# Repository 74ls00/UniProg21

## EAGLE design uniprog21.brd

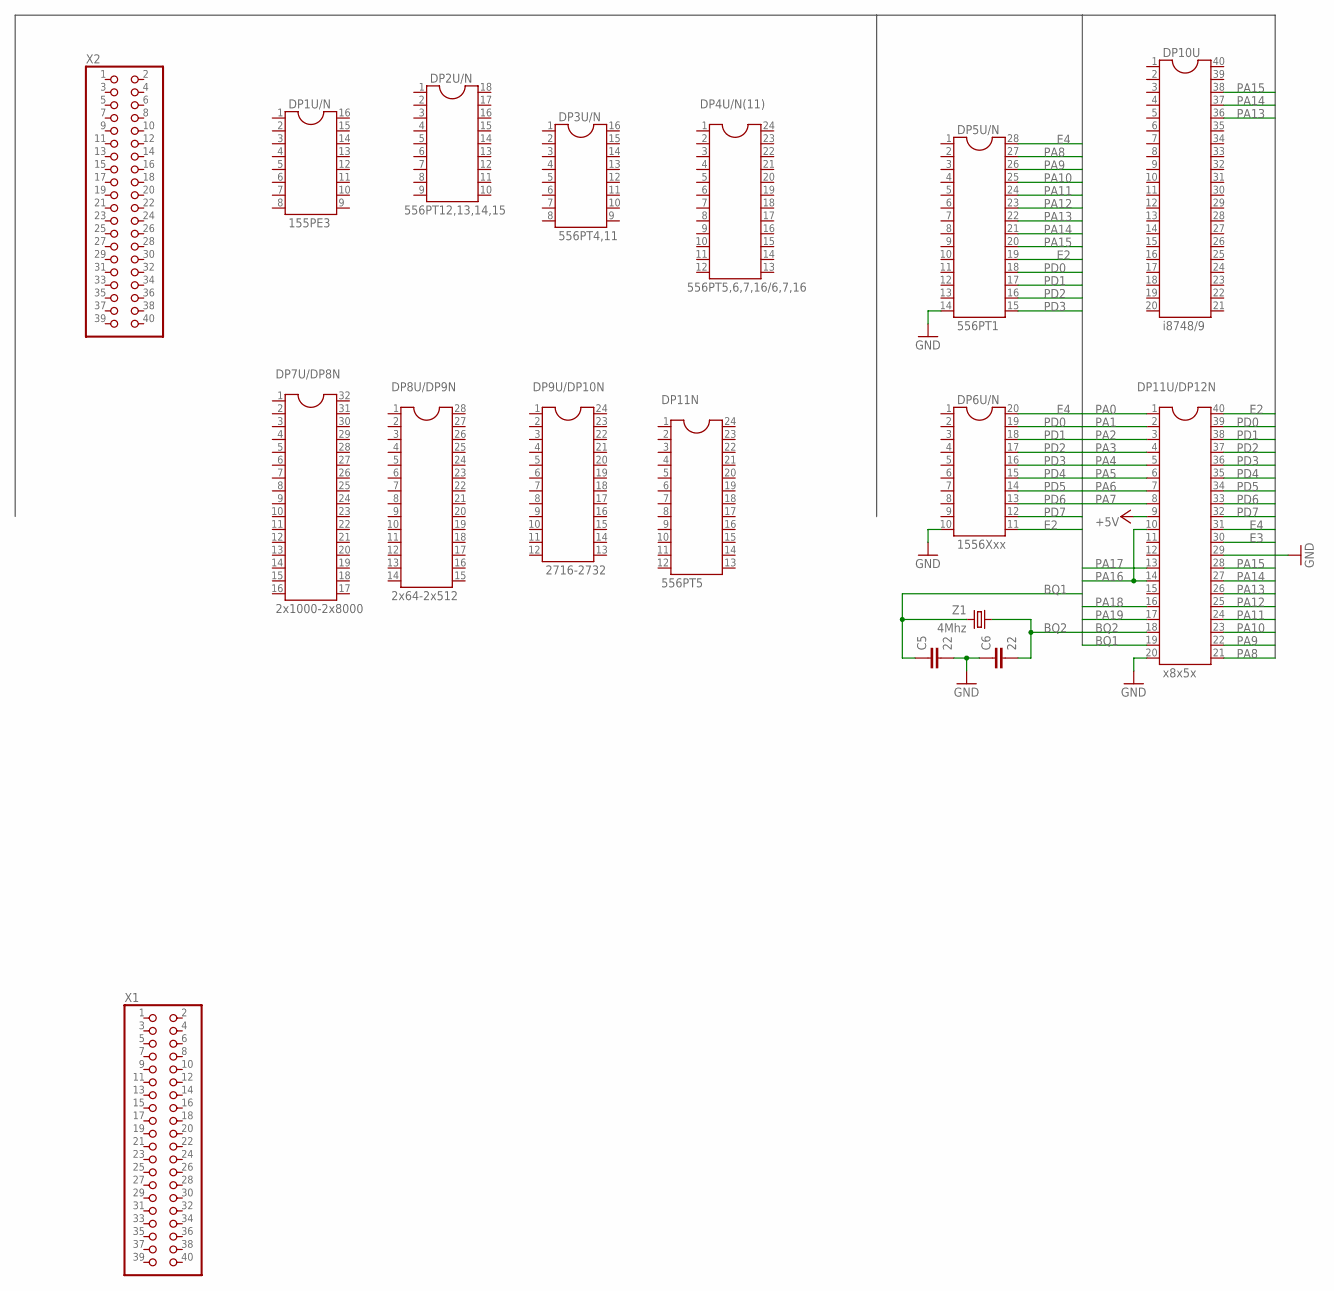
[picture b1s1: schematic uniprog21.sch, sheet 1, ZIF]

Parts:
C5, C6: 22; C0805
DP1U/N: 155РЕ3; SOCKET-16
DP2U/N: 556РТ12,13,14,15; SOCKET-18
DP3U/N: 556РТ4,11; SOCKET-16
DP4U/N(11): 556РТ5,6,7,16/6,7,16; DIL24-6
DP5U/N: 556РТ1; DIL28-6
DP6U/N: 1556Хxx; SOCKET-20
DP7U/DP8N: 2x1000-2x8000; DIL32
DP8U/DP9N: 2x64-2x512; DIL28-6
DP9U/DP10N: 2716-2732; DIL24-6
DP10U: i8748/9; DIL40
DP11N: 556РТ5; DIL24-6
DP11U/DP12N: x8x5x; DIL40
X1, X2: PINHD-2X20; 2X20
Z1: 4Mhz; HC49U-LM

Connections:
+5V: DP11U/DP12N.9; also elsewhere on the board
BQ1: C5.1, DP11U/DP12N.19, Z1.2
BQ2: C6.2, DP11U/DP12N.18, Z1.1
E2: DP5U/N.19, DP6U/N.11, DP11U/DP12N.40; also elsewhere on the board
E3: DP11U/DP12N.30; also elsewhere on the board
E4: DP5U/N.28, DP6U/N.20, DP11U/DP12N.31; also elsewhere on the board
GND: C5.2, C6.1, DP5U/N.14, DP6U/N.10, DP11U/DP12N.20, DP11U/DP12N.29; also elsewhere on the board
PA0: DP11U/DP12N.1; also elsewhere on the board
PA1: DP11U/DP12N.2; also elsewhere on the board
PA2: DP11U/DP12N.3
PA3: DP11U/DP12N.4
PA4: DP11U/DP12N.5
PA5: DP11U/DP12N.6
PA6: DP11U/DP12N.7
PA7: DP11U/DP12N.8
PA8: DP5U/N.27, DP11U/DP12N.21
PA9: DP5U/N.26, DP11U/DP12N.22
PA10: DP5U/N.25, DP11U/DP12N.23
PA11: DP5U/N.24, DP11U/DP12N.24
PA12: DP5U/N.23, DP11U/DP12N.25
PA13: DP5U/N.22, DP10U.36, DP11U/DP12N.26
PA14: DP5U/N.21, DP10U.37, DP11U/DP12N.27
PA15: DP5U/N.20, DP10U.38, DP11U/DP12N.28
PA16: DP11U/DP12N.10, DP11U/DP12N.14
PA17: DP11U/DP12N.13
PA18: DP11U/DP12N.16
PA19: DP11U/DP12N.17
PD0: DP5U/N.18, DP6U/N.19, DP11U/DP12N.39
PD1: DP5U/N.17, DP6U/N.18, DP11U/DP12N.38
PD2: DP5U/N.16, DP6U/N.17, DP11U/DP12N.37
PD3: DP5U/N.15, DP6U/N.16, DP11U/DP12N.36
PD4: DP6U/N.15, DP11U/DP12N.35
PD5: DP6U/N.14, DP11U/DP12N.34
PD6: DP6U/N.13, DP11U/DP12N.33
PD7: DP6U/N.12, DP11U/DP12N.32

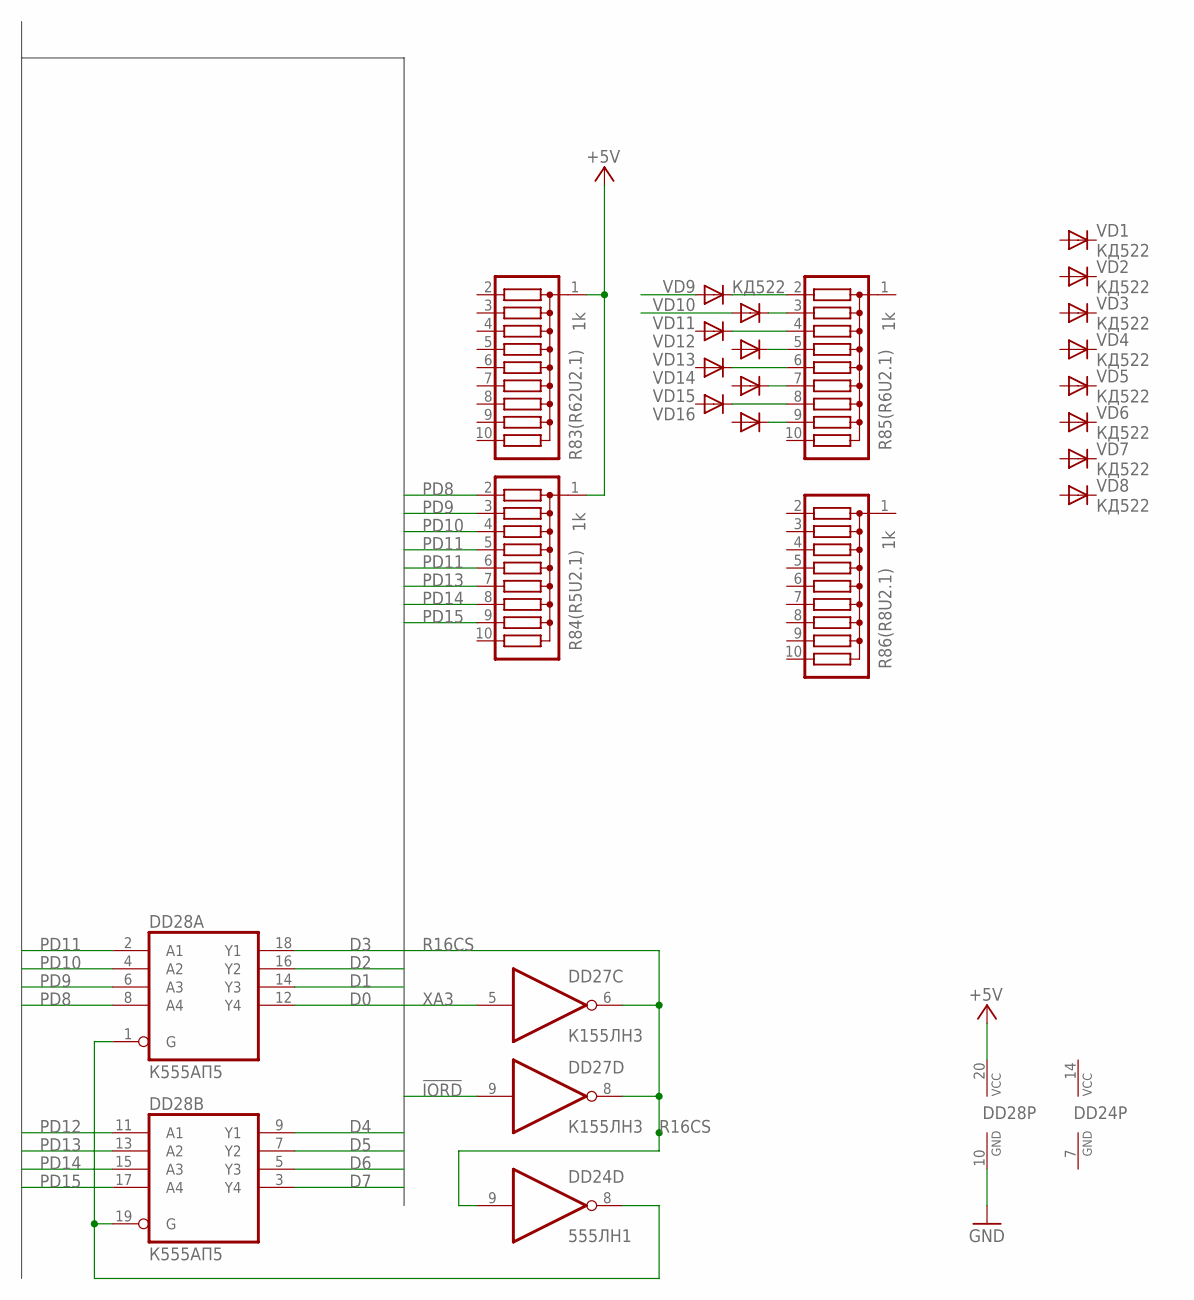
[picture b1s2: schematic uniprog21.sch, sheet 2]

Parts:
DD24: 555ЛН1; DIL14
DD27: К155ЛН3; DIL14
DD28: К555АП5; DIL20
R83(R62U2.1), R84(R5U2.1), R85(R6U2.1), R86(R8U2.1): 1k; SIL10
VD1, VD2, VD3, VD4, VD5, VD6, VD7, VD8, VD9, VD10, VD11, VD12, VD13, VD14, VD15, VD16: КД522; DO35-7

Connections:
!IORD: DD27.9 (I); also elsewhere on the board
+5V: DD28.20 (VCC), R83(R62U2.1).1, R84(R5U2.1).1; also elsewhere on the board
D0: DD28.12 (Y4); also elsewhere on the board
D1: DD28.14 (Y3); also elsewhere on the board
D2: DD28.16 (Y2); also elsewhere on the board
D3: DD28.18 (Y1); also elsewhere on the board
D4: DD28.9 (Y1); also elsewhere on the board
D5: DD28.7 (Y2); also elsewhere on the board
D6: DD28.5 (Y3); also elsewhere on the board
D7: DD28.3 (Y4); also elsewhere on the board
GND: DD24.7 (GND), DD28.10 (GND); also elsewhere on the board
unnamed: R85(R6U2.1).2, VD9.C
unnamed: DD24.8 (O), DD28.1 (G), DD28.19 (G)
unnamed: R85(R6U2.1).3, VD10.C
unnamed: R85(R6U2.1).4, VD11.C
unnamed: R85(R6U2.1).5, VD12.C
unnamed: R85(R6U2.1).6, VD13.C
unnamed: R85(R6U2.1).7, VD14.C
unnamed: R85(R6U2.1).8, VD15.C
unnamed: R85(R6U2.1).9, VD16.C
PD8: DD28.8 (A4), R84(R5U2.1).2
PD9: DD28.6 (A3), R84(R5U2.1).3
PD10: DD28.4 (A2), R84(R5U2.1).4
PD11: DD28.2 (A1), R84(R5U2.1).5, R84(R5U2.1).6
PD12: DD28.11 (A1)
PD13: DD28.13 (A2), R84(R5U2.1).7
PD14: DD28.15 (A3), R84(R5U2.1).8
PD15: DD28.17 (A4), R84(R5U2.1).9
R16CS: DD24.9 (I), DD27.6 (O), DD27.8 (O)
VCC: DD24.14 (VCC); also elsewhere on the board
XA3: DD27.5 (I); also elsewhere on the board

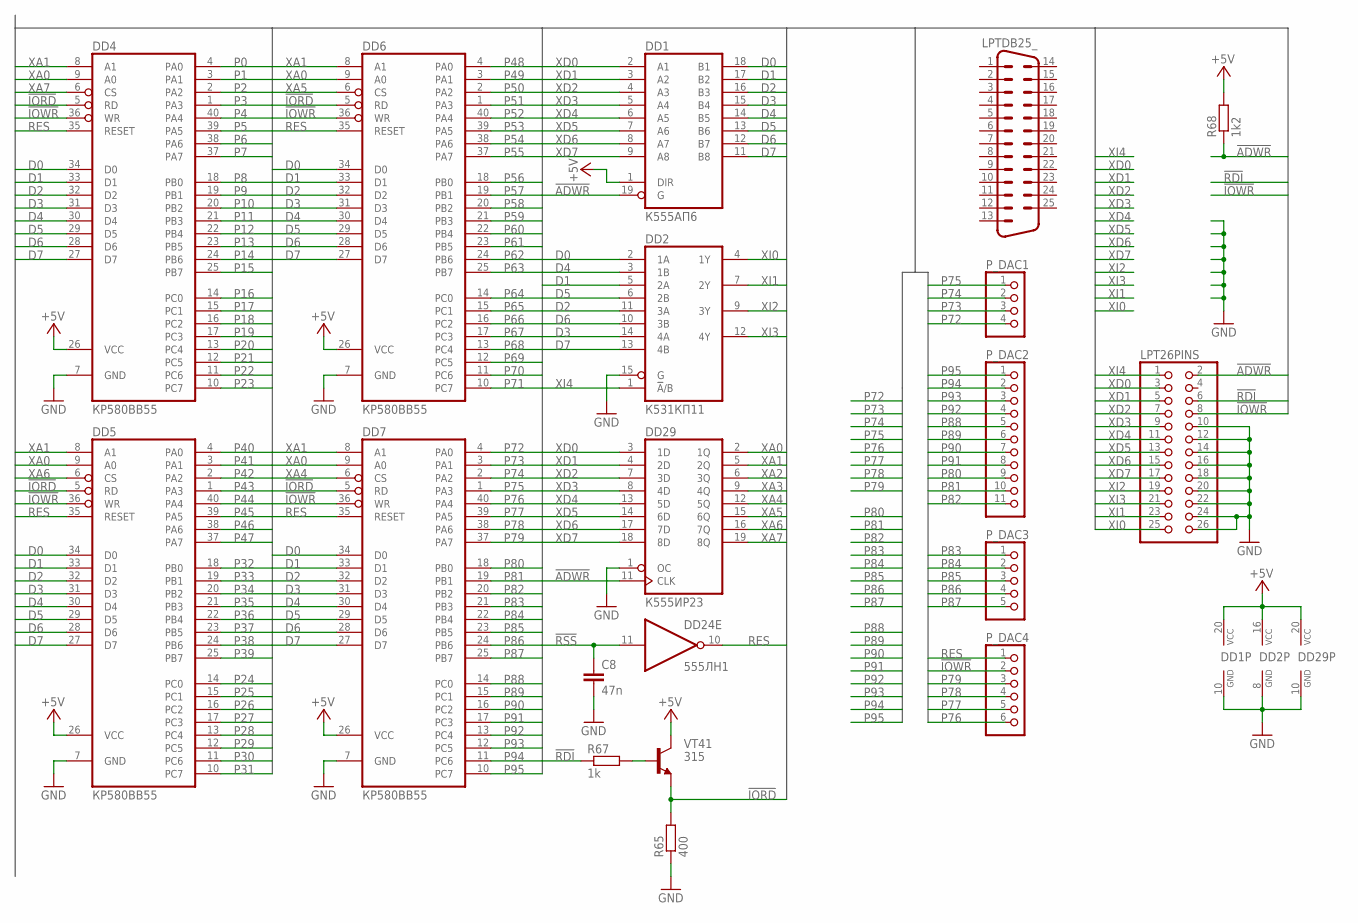
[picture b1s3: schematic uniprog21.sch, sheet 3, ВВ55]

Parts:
C8: 47n; C0805
DD1: К555АП6; DIL20
DD2: К531КП11; DIL16
DD4, DD5, DD6, DD7: КР580ВВ55; DIL40
DD24: 555ЛН1; DIL14
DD29: К555ИР23; DIL20
LPT26PINS: PINHD-2X13; 2X13
LPTDB25_: M25HP
P_DAC1: PINHD-1X4; 1X04
P_DAC2: PINHD-1X11; 1X11
P_DAC3: PINHD-1X5; 1X05
P_DAC4: PINHD-1X6; 1X06
R65: 400; R0805
R67: 1k; R0805
R68: 1k2; R0805
VT41: 315; SOT23

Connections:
!ADWR: DD1.19 (G), DD29.11 (CLK), LPT26PINS.2, R68.1
!IORD: DD4.5 (RD), DD5.5 (RD), DD6.5 (RD), DD7.5 (RD), R65.2, VT41.2 (E); also elsewhere on the board
!IOWR: DD4.36 (WR), DD5.36 (WR), DD6.36 (WR), DD7.36 (WR), LPT26PINS.8, P_DAC4.2
!RDI: LPT26PINS.6, R67.1
!RSS: C8.1, DD24.11 (I)
+5V: DD1.1 (DIR), DD1.20 (VCC), DD2.16 (VCC), DD4.26 (VCC), DD5.26 (VCC), DD6.26 (VCC), DD7.26 (VCC), DD29.20 (VCC), R68.2, VT41.3 (C); also elsewhere on the board
D0: DD1.18 (B1), DD2.2 (1A), DD4.34 (D0), DD5.34 (D0), DD6.34 (D0), DD7.34 (D0); also elsewhere on the board
D1: DD1.17 (B2), DD2.5 (2A), DD4.33 (D1), DD5.33 (D1), DD6.33 (D1), DD7.33 (D1); also elsewhere on the board
D2: DD1.16 (B3), DD2.11 (3A), DD4.32 (D2), DD5.32 (D2), DD6.32 (D2), DD7.32 (D2); also elsewhere on the board
D3: DD1.15 (B4), DD2.14 (4A), DD4.31 (D3), DD5.31 (D3), DD6.31 (D3), DD7.31 (D3); also elsewhere on the board
D4: DD1.14 (B5), DD2.3 (1B), DD4.30 (D4), DD5.30 (D4), DD6.30 (D4), DD7.30 (D4); also elsewhere on the board
D5: DD1.13 (B6), DD2.6 (2B), DD4.29 (D5), DD5.29 (D5), DD6.29 (D5), DD7.29 (D5); also elsewhere on the board
D6: DD1.12 (B7), DD2.10 (3B), DD4.28 (D6), DD5.28 (D6), DD6.28 (D6), DD7.28 (D6); also elsewhere on the board
D7: DD1.11 (B8), DD2.13 (4B), DD4.27 (D7), DD5.27 (D7), DD6.27 (D7), DD7.27 (D7); also elsewhere on the board
GND: C8.2, DD1.10 (GND), DD2.8 (GND), DD2.15 (G), DD4.7 (GND), DD5.7 (GND), DD6.7 (GND), DD7.7 (GND), DD24.7 (GND), DD29.1 (OC), DD29.10 (GND), LPT26PINS.10, LPT26PINS.12, LPT26PINS.14, LPT26PINS.16, LPT26PINS.18, LPT26PINS.20, LPT26PINS.22, LPT26PINS.24, LPT26PINS.26, R65.1; also elsewhere on the board
unnamed: R67.2, VT41.1 (B)
P0: DD4.4 (PA0); also elsewhere on the board
P1: DD4.3 (PA1); also elsewhere on the board
P2: DD4.2 (PA2)
P3: DD4.1 (PA3)
P4: DD4.40 (PA4)
P5: DD4.39 (PA5)
P6: DD4.38 (PA6)
P7: DD4.37 (PA7)
P8: DD4.18 (PB0); also elsewhere on the board
P9: DD4.19 (PB1); also elsewhere on the board
P10: DD4.20 (PB2)
P11: DD4.21 (PB3)
P12: DD4.22 (PB4)
P13: DD4.23 (PB5)
P14: DD4.24 (PB6)
P15: DD4.25 (PB7)
P16: DD4.14 (PC0)
P17: DD4.15 (PC1)
P18: DD4.16 (PC2)
P19: DD4.17 (PC3)
P20: DD4.13 (PC4)
P21: DD4.12 (PC5)
P22: DD4.11 (PC6)
P23: DD4.10 (PC7)
P24: DD5.14 (PC0)
P25: DD5.15 (PC1)
P26: DD5.16 (PC2)
P27: DD5.17 (PC3)
P28: DD5.13 (PC4)
P29: DD5.12 (PC5)
P30: DD5.11 (PC6)
P31: DD5.10 (PC7)
P32: DD5.18 (PB0)
P33: DD5.19 (PB1)
P34: DD5.20 (PB2)
P35: DD5.21 (PB3)
P36: DD5.22 (PB4)
P37: DD5.23 (PB5)
P38: DD5.24 (PB6)
P39: DD5.25 (PB7)
P40: DD5.4 (PA0)
P41: DD5.3 (PA1)
P42: DD5.2 (PA2)
P43: DD5.1 (PA3)
P44: DD5.40 (PA4)
P45: DD5.39 (PA5)
P46: DD5.38 (PA6)
P47: DD5.37 (PA7)
P48: DD6.4 (PA0)
P49: DD6.3 (PA1)
P50: DD6.2 (PA2)
P51: DD6.1 (PA3)
P52: DD6.40 (PA4)
P53: DD6.39 (PA5)
P54: DD6.38 (PA6)
P55: DD6.37 (PA7)
P56: DD6.18 (PB0)
P57: DD6.19 (PB1)
P58: DD6.20 (PB2)
P59: DD6.21 (PB3)
P60: DD6.22 (PB4)
P61: DD6.23 (PB5)
P62: DD6.24 (PB6)
P63: DD6.25 (PB7)
P64: DD6.14 (PC0); also elsewhere on the board
P65: DD6.15 (PC1); also elsewhere on the board
P66: DD6.16 (PC2); also elsewhere on the board
P67: DD6.17 (PC3); also elsewhere on the board
P68: DD6.13 (PC4); also elsewhere on the board
P69: DD6.12 (PC5); also elsewhere on the board
P70: DD6.11 (PC6); also elsewhere on the board
P71: DD6.10 (PC7); also elsewhere on the board
P72: DD7.4 (PA0), P_DAC1.4; also elsewhere on the board
P73: DD7.3 (PA1), P_DAC1.3; also elsewhere on the board
P74: DD7.2 (PA2), P_DAC1.2; also elsewhere on the board
P75: DD7.1 (PA3), P_DAC1.1; also elsewhere on the board
P76: DD7.40 (PA4), P_DAC4.6; also elsewhere on the board
P77: DD7.39 (PA5), P_DAC4.5; also elsewhere on the board
P78: DD7.38 (PA6), P_DAC4.4; also elsewhere on the board
P79: DD7.37 (PA7), P_DAC4.3; also elsewhere on the board
P80: DD7.18 (PB0), P_DAC2.9; also elsewhere on the board
P81: DD7.19 (PB1), P_DAC2.10; also elsewhere on the board
P82: DD7.20 (PB2), P_DAC2.11; also elsewhere on the board
P83: DD7.21 (PB3), P_DAC3.1; also elsewhere on the board
P84: DD7.22 (PB4), P_DAC3.2; also elsewhere on the board
P85: DD7.23 (PB5), P_DAC3.3; also elsewhere on the board
P86: DD7.24 (PB6), P_DAC3.4; also elsewhere on the board
P87: DD7.25 (PB7), P_DAC3.5; also elsewhere on the board
P88: DD7.14 (PC0), P_DAC2.5; also elsewhere on the board
P89: DD7.15 (PC1), P_DAC2.6; also elsewhere on the board
P90: DD7.16 (PC2), P_DAC2.7; also elsewhere on the board
P91: DD7.17 (PC3), P_DAC2.8; also elsewhere on the board
P92: DD7.13 (PC4), P_DAC2.4; also elsewhere on the board
P93: DD7.12 (PC5), P_DAC2.3; also elsewhere on the board
P94: DD7.11 (PC6), P_DAC2.2; also elsewhere on the board
P95: DD7.10 (PC7), P_DAC2.1; also elsewhere on the board
RES: DD4.35 (RESET), DD5.35 (RESET), DD6.35 (RESET), DD7.35 (RESET), DD24.10 (O), P_DAC4.1
VCC: DD24.14 (VCC); also elsewhere on the board
XA0: DD4.9 (A0), DD5.9 (A0), DD6.9 (A0), DD7.9 (A0), DD29.2 (1Q)
XA1: DD4.8 (A1), DD5.8 (A1), DD6.8 (A1), DD7.8 (A1), DD29.5 (2Q)
XA2: DD29.6 (3Q)
XA3: DD29.9 (4Q); also elsewhere on the board
XA4: DD7.6 (CS), DD29.12 (5Q)
XA5: DD6.6 (CS), DD29.15 (6Q)
XA6: DD5.6 (CS), DD29.16 (7Q)
XA7: DD4.6 (CS), DD29.19 (8Q)
XD0: DD1.2 (A1), DD29.3 (1D), LPT26PINS.3
XD1: DD1.3 (A2), DD29.4 (2D), LPT26PINS.5
XD2: DD1.4 (A3), DD29.7 (3D), LPT26PINS.7
XD3: DD1.5 (A4), DD29.8 (4D), LPT26PINS.9
XD4: DD1.6 (A5), DD29.13 (5D), LPT26PINS.11
XD5: DD1.7 (A6), DD29.14 (6D), LPT26PINS.13
XD6: DD1.8 (A7), DD29.17 (7D), LPT26PINS.15
XD7: DD1.9 (A8), DD29.18 (8D), LPT26PINS.17
XI0: DD2.4 (1Y), LPT26PINS.25
XI1: DD2.7 (2Y), LPT26PINS.23
XI2: DD2.9 (3Y), LPT26PINS.19
XI3: DD2.12 (4Y), LPT26PINS.21
XI4: DD2.1 (!A!/B), LPT26PINS.1

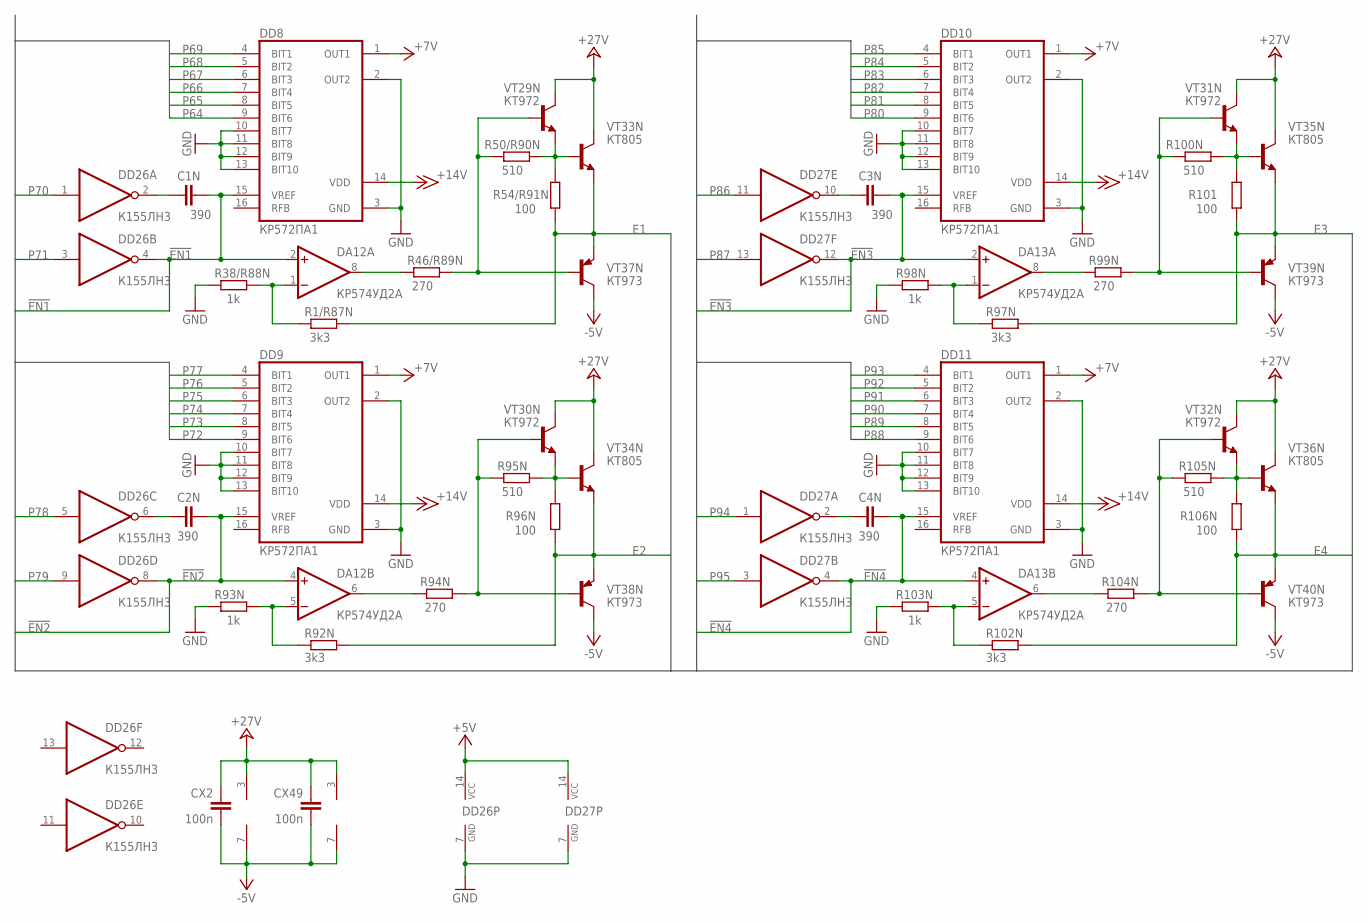
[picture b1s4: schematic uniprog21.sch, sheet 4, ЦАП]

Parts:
C1N, C2N, C3N, C4N: 390; C0805
CX2, CX49: 100n; C0805
DA12, DA13: КР574УД2А; DIL08
DD8, DD9, DD10, DD11: КР572ПА1; DIL16
DD26, DD27: К155ЛН3; DIL14
R1/R87N, R92N, R97N, R102N: 3k3; R0805
R38/R88N, R93N, R98N, R103N: 1k; R0805
R46/R89N, R94N, R99N, R104N: 270; R0805
R50/R90N, R95N, R100N, R105N: 510; R0805
R54/R91N, R96N, R101, R106N: 100; R0805
VT29N, VT30N, VT31N, VT32N: КТ972; TO126V
VT33N, VT34N, VT35N, VT36N: КТ805; TO220FV
VT37N, VT38N, VT39N, VT40N: КТ973; TO126V

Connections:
!EN1: C1N.2, DA12.2 (+IN), DD8.15 (VREF), DD26.4 (O)
!EN2: C2N.2, DA12.4 (+IN), DD9.15 (VREF), DD26.8 (O)
!EN3: C3N.2, DA13.2 (+IN), DD10.15 (VREF), DD27.12 (O)
!EN4: C4N.2, DA13.4 (+IN), DD11.15 (VREF), DD27.4 (O)
+5V: DD26.14 (VCC), DD27.14 (VCC); also elsewhere on the board
+7V: DD8.1 (OUT1), DD9.1 (OUT1), DD10.1 (OUT1), DD11.1 (OUT1)
+14V: DD8.14 (VDD), DD9.14 (VDD), DD10.14 (VDD), DD11.14 (VDD)
+27V: CX2.1, CX49.1, DA12.3 (V+), DA13.3 (V+), VT29N.2 (C), VT30N.2 (C), VT31N.2 (C), VT32N.2 (C), VT33N.2 (C), VT34N.2 (C), VT35N.2 (C), VT36N.2 (C)
-5V: CX2.2, CX49.2, DA12.7 (V-), DA13.7 (V-), VT37N.2 (C), VT38N.2 (C), VT39N.2 (C), VT40N.2 (C)
E1: R1/R87N.2, R54/R91N.1, VT33N.1 (E), VT37N.1 (E); also elsewhere on the board
E2: R92N.2, R96N.1, VT34N.1 (E), VT38N.1 (E); also elsewhere on the board
E3: R97N.2, R101.1, VT35N.1 (E), VT39N.1 (E); also elsewhere on the board
E4: R102N.2, R106N.1, VT36N.1 (E), VT40N.1 (E); also elsewhere on the board
GND: DD8.2 (OUT2), DD8.3 (GND), DD8.10 (BIT7), DD8.11 (BIT8), DD8.12 (BIT9), DD8.13 (BIT10), DD9.2 (OUT2), DD9.3 (GND), DD9.10 (BIT7), DD9.11 (BIT8), DD9.12 (BIT9), DD9.13 (BIT10), DD10.2 (OUT2), DD10.3 (GND), DD10.10 (BIT7), DD10.11 (BIT8), DD10.12 (BIT9), DD10.13 (BIT10), DD11.2 (OUT2), DD11.3 (GND), DD11.10 (BIT7), DD11.11 (BIT8), DD11.12 (BIT9), DD11.13 (BIT10), DD26.7 (GND), DD27.7 (GND), R38/R88N.1, R93N.1, R98N.1, R103N.1; also elsewhere on the board
unnamed: C1N.1, DD26.2 (O)
unnamed: C3N.1, DD27.10 (O)
unnamed: DA12.8 (OUT), R46/R89N.1
unnamed: DA13.8 (OUT), R99N.1
unnamed: DA12.1 (-IN), R1/R87N.1, R38/R88N.2
unnamed: R50/R90N.2, R54/R91N.2, VT29N.1 (E), VT33N.3 (B)
unnamed: DA13.1 (-IN), R97N.1, R98N.2
unnamed: R100N.2, R101.2, VT31N.1 (E), VT35N.3 (B)
unnamed: R46/R89N.2, R50/R90N.1, VT29N.3 (B), VT37N.3 (B)
unnamed: C2N.1, DD26.6 (O)
unnamed: DA12.6 (OUT), R94N.1
unnamed: DA12.5 (-IN), R92N.1, R93N.2
unnamed: R95N.2, R96N.2, VT30N.1 (E), VT34N.3 (B)
unnamed: R94N.2, R95N.1, VT30N.3 (B), VT38N.3 (B)
unnamed: R99N.2, R100N.1, VT31N.3 (B), VT39N.3 (B)
unnamed: C4N.1, DD27.2 (O)
unnamed: DA13.6 (OUT), R104N.1
unnamed: DA13.5 (-IN), R102N.1, R103N.2
unnamed: R105N.2, R106N.2, VT32N.1 (E), VT36N.3 (B)
unnamed: R104N.2, R105N.1, VT32N.3 (B), VT40N.3 (B)
P64: DD8.9 (BIT6); also elsewhere on the board
P65: DD8.8 (BIT5); also elsewhere on the board
P66: DD8.7 (BIT4); also elsewhere on the board
P67: DD8.6 (BIT3); also elsewhere on the board
P68: DD8.5 (BIT2); also elsewhere on the board
P69: DD8.4 (BIT1); also elsewhere on the board
P70: DD26.1 (I); also elsewhere on the board
P71: DD26.3 (I); also elsewhere on the board
P72: DD9.9 (BIT6); also elsewhere on the board
P73: DD9.8 (BIT5); also elsewhere on the board
P74: DD9.7 (BIT4); also elsewhere on the board
P75: DD9.6 (BIT3); also elsewhere on the board
P76: DD9.5 (BIT2); also elsewhere on the board
P77: DD9.4 (BIT1); also elsewhere on the board
P78: DD26.5 (I); also elsewhere on the board
P79: DD26.9 (I); also elsewhere on the board
P80: DD10.9 (BIT6); also elsewhere on the board
P81: DD10.8 (BIT5); also elsewhere on the board
P82: DD10.7 (BIT4); also elsewhere on the board
P83: DD10.6 (BIT3); also elsewhere on the board
P84: DD10.5 (BIT2); also elsewhere on the board
P85: DD10.4 (BIT1); also elsewhere on the board
P86: DD27.11 (I); also elsewhere on the board
P87: DD27.13 (I); also elsewhere on the board
P88: DD11.9 (BIT6); also elsewhere on the board
P89: DD11.8 (BIT5); also elsewhere on the board
P90: DD11.7 (BIT4); also elsewhere on the board
P91: DD11.6 (BIT3); also elsewhere on the board
P92: DD11.5 (BIT2); also elsewhere on the board
P93: DD11.4 (BIT1); also elsewhere on the board
P94: DD27.1 (I); also elsewhere on the board
P95: DD27.3 (I); also elsewhere on the board

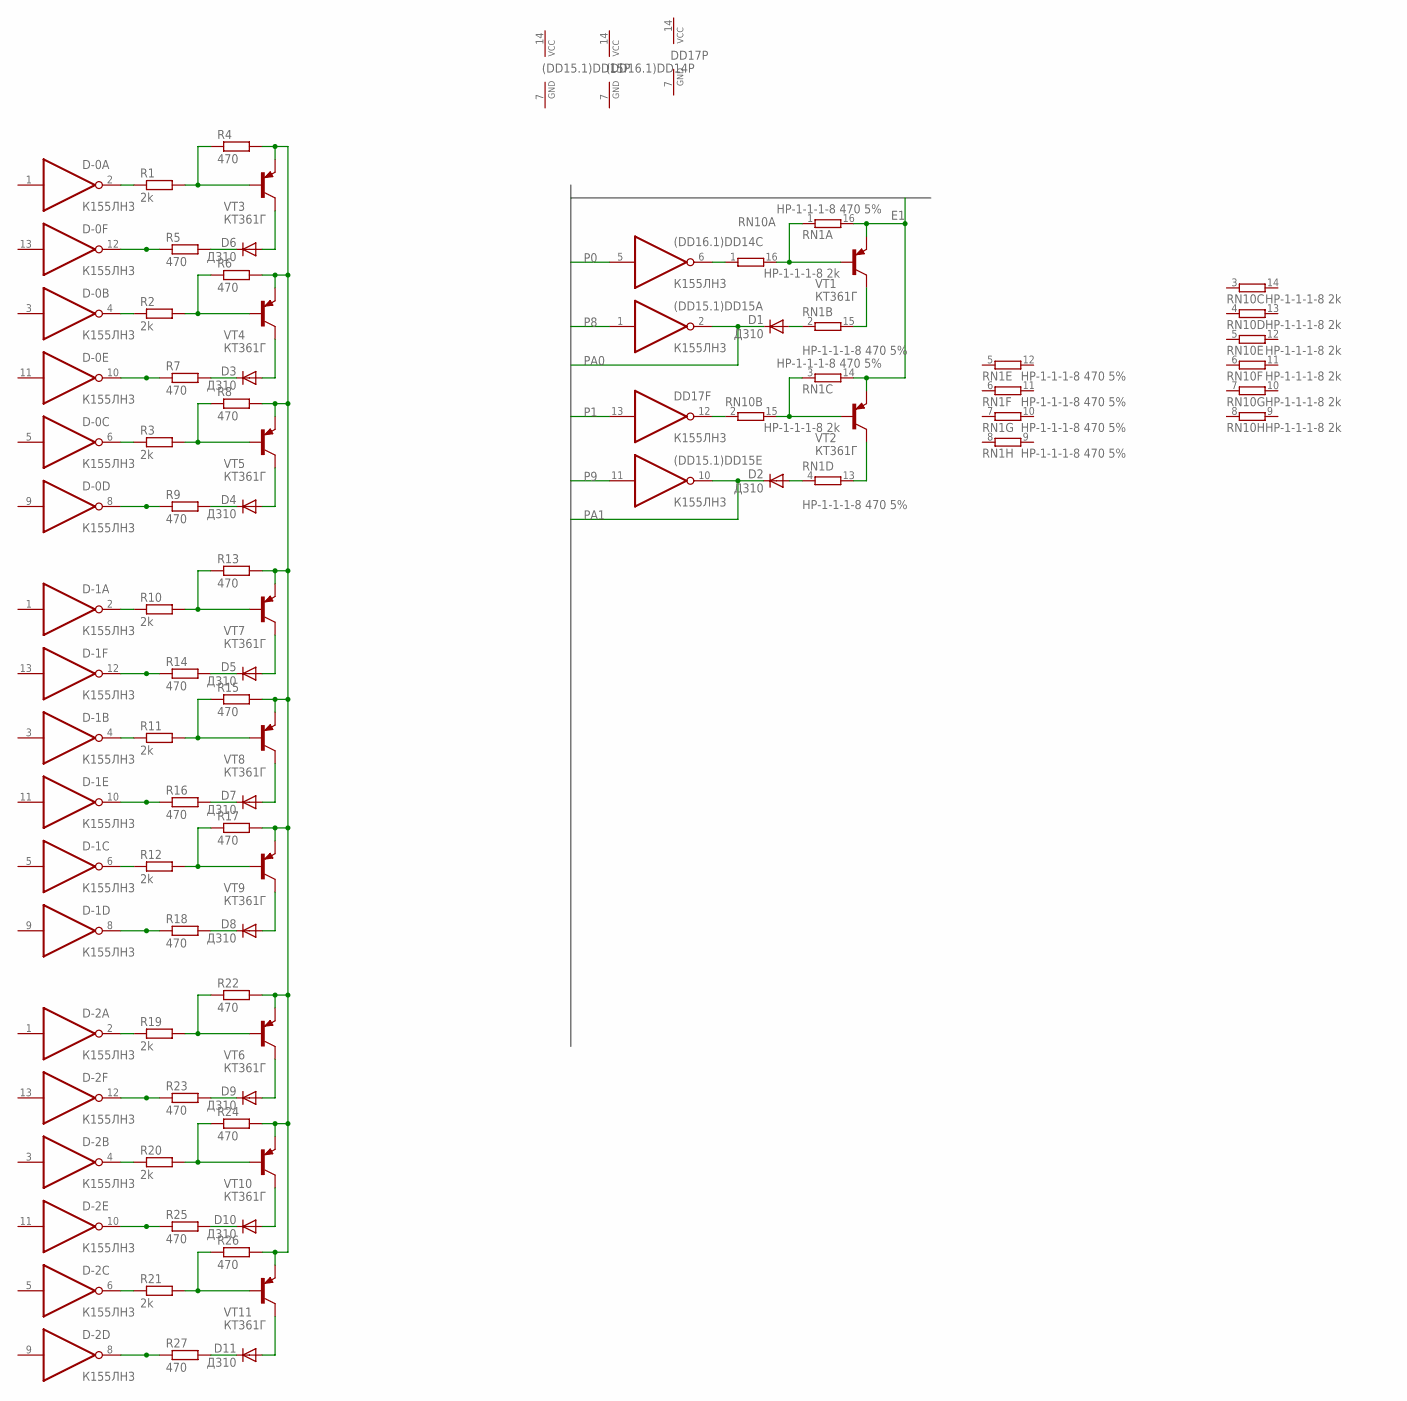
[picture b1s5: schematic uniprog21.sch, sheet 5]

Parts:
(DD15.1)DD15, (DD16.1)DD14: К155ЛН3; DIL14
D1, D2, D3, D4, D5, D6, D7, D8, D9, D10, D11: Д310; DO15-12
D-0, D-1, D-2: К155ЛН3; DIL14
DD17: К155ЛН3; DIL14
R1, R2, R3, R10, R11, R12, R19, R20, R21: 2k; R0805
R4, R5, R6, R7, R8, R9, R13, R14, R15, R16, R17, R18, R22, R23, R24, R25, R26, R27: 470; R0805
RN1: НР-1-1-1-8 470 5%; DIL16
RN10: НР-1-1-1-8 2k; DIL16
VT1, VT2, VT3, VT4, VT5, VT6, VT7, VT8, VT9, VT10, VT11: КТ361Г; TO92

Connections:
E1: R4.2, R6.2, R8.2, R13.2, R15.2, R17.2, R22.2, R24.2, R26.2, RN1.14 (2), RN1.16 (2), VT1.1 (E), VT2.1 (E), VT3.1 (E), VT4.1 (E), VT5.1 (E), VT6.1 (E), VT7.1 (E), VT8.1 (E), VT9.1 (E), VT10.1 (E), VT11.1 (E); also elsewhere on the board
GND: (DD15.1)DD15.7 (GND), (DD16.1)DD14.7 (GND), D-0.7 (GND), D-1.7 (GND), D-2.7 (GND), DD17.7 (GND); also elsewhere on the board
unnamed: (DD16.1)DD14.6 (O), RN10.1
unnamed: RN1.15 (2), VT1.2 (C)
unnamed: RN1.1, RN10.16 (2), VT1.3 (B)
unnamed: DD17.12 (O), RN10.2 (1)
unnamed: RN1.13 (2), VT2.2 (C)
unnamed: RN1.3 (1), RN10.15 (2), VT2.3 (B)
unnamed: D1.A, RN1.2 (1)
unnamed: D2.A, RN1.4 (1)
unnamed: R1.2, R4.1, VT3.3 (B)
unnamed: D6.A, VT3.2 (C)
unnamed: D6.C, R5.2
unnamed: D-0.2 (O), R1.1
unnamed: R2.2, R6.1, VT4.3 (B)
unnamed: D3.A, VT4.2 (C)
unnamed: D-0.12 (O), R5.1
unnamed: R3.2, R8.1, VT5.3 (B)
unnamed: D4.A, VT5.2 (C)
unnamed: D-0.8 (O), R9.1
unnamed: D-0.6 (O), R3.1
unnamed: D-0.4 (O), R2.1
unnamed: D4.C, R9.2
unnamed: D3.C, R7.2
unnamed: D-0.10 (O), R7.1
unnamed: R10.2, R13.1, VT7.3 (B)
unnamed: D5.A, VT7.2 (C)
unnamed: D-1.2 (O), R10.1
unnamed: R11.2, R15.1, VT8.3 (B)
unnamed: D7.A, VT8.2 (C)
unnamed: R12.2, R17.1, VT9.3 (B)
unnamed: D8.A, VT9.2 (C)
unnamed: D-1.6 (O), R12.1
unnamed: D-1.4 (O), R11.1
unnamed: D5.C, R14.2
unnamed: D-1.12 (O), R14.1
unnamed: D-1.8 (O), R18.1
unnamed: D8.C, R18.2
unnamed: D7.C, R16.2
unnamed: D-1.10 (O), R16.1
unnamed: R19.2, R22.1, VT6.3 (B)
unnamed: D9.A, VT6.2 (C)
unnamed: D-2.2 (O), R19.1
unnamed: R20.2, R24.1, VT10.3 (B)
unnamed: D10.A, VT10.2 (C)
unnamed: R21.2, R26.1, VT11.3 (B)
unnamed: D11.A, VT11.2 (C)
unnamed: D-2.6 (O), R21.1
unnamed: D-2.4 (O), R20.1
unnamed: D9.C, R23.2
unnamed: D-2.12 (O), R23.1
unnamed: D-2.8 (O), R27.1
unnamed: D11.C, R27.2
unnamed: D10.C, R25.2
unnamed: D-2.10 (O), R25.1
P0: (DD16.1)DD14.5 (I); also elsewhere on the board
P1: DD17.13 (I); also elsewhere on the board
P8: (DD15.1)DD15.1 (I); also elsewhere on the board
P9: (DD15.1)DD15.11 (I); also elsewhere on the board
PA0: (DD15.1)DD15.2 (O), D1.C; also elsewhere on the board
PA1: (DD15.1)DD15.10 (O), D2.C; also elsewhere on the board
VCC: (DD15.1)DD15.14 (VCC), (DD16.1)DD14.14 (VCC), D-0.14 (VCC), D-1.14 (VCC), D-2.14 (VCC), DD17.14 (VCC); also elsewhere on the board

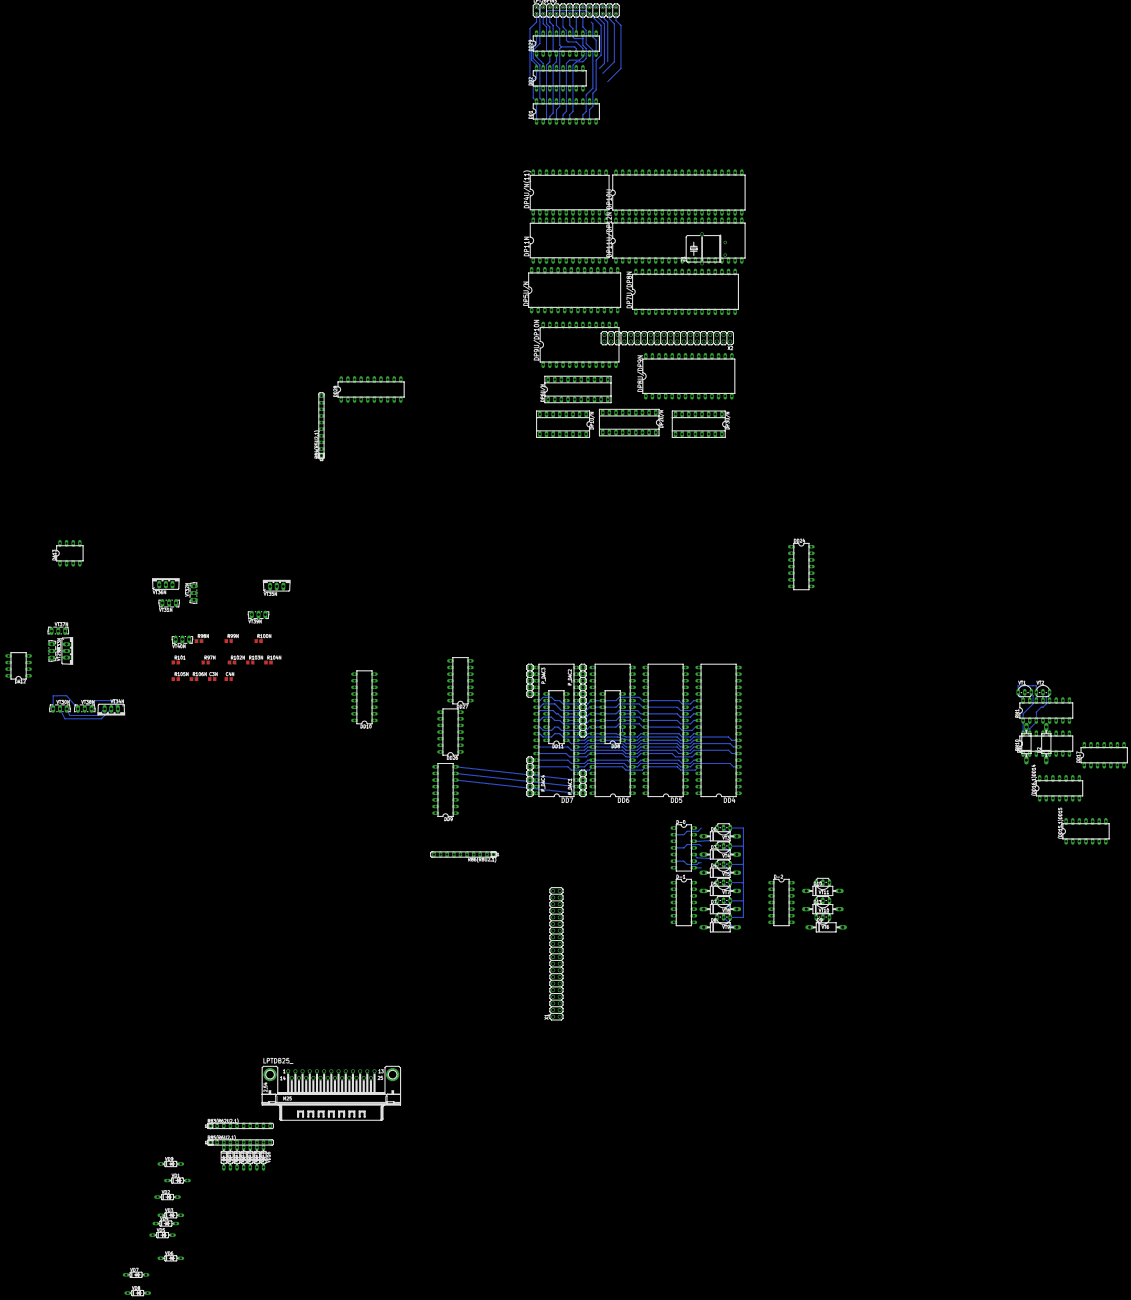
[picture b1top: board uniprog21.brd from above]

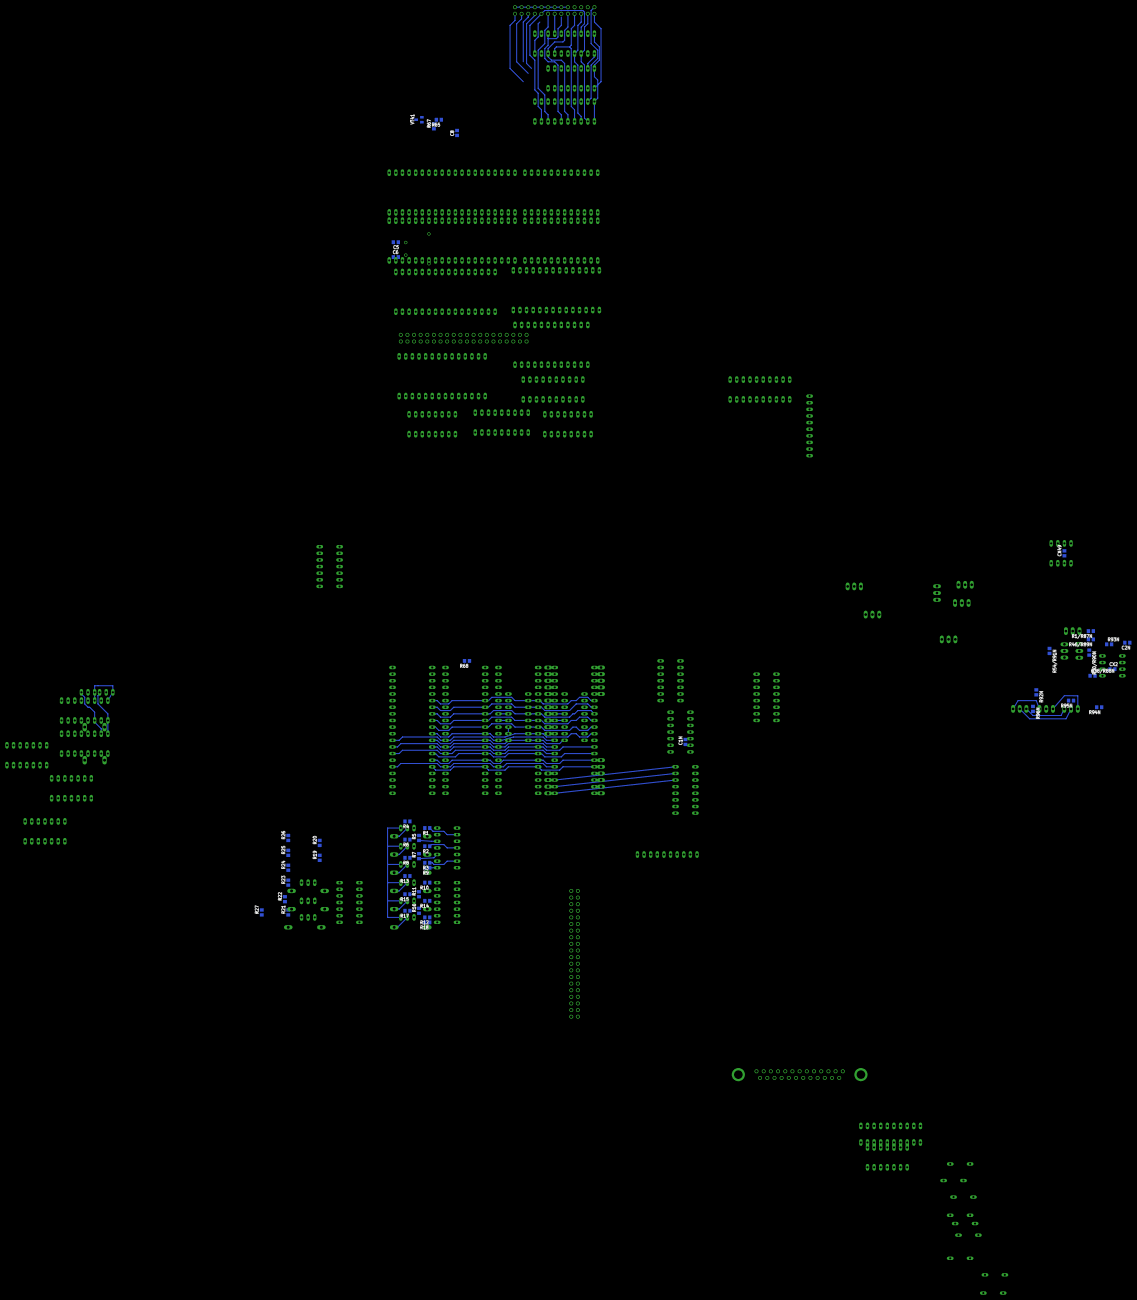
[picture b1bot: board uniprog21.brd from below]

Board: 2 copper layers, 160 parts (48 on the bottom side), 197 nets.
